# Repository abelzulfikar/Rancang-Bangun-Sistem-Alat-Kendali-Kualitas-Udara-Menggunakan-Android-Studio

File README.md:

# Rancang-Bangun-Sistem-Alat-Kendali-Kualitas-Udara-Menggunakan-Android-Studio
memantau dan mengatur kualitas udara dalam ruangan melalui aplikasi Android

Latar Belakang
Kualitas udara dalam ruangan memiliki dampak besar pada kesehatan dan kenyamanan manusia sehari-hari. Udara yang tercemar dapat menyebabkan gangguan pernapasan, alergi, dan dampak negatif lainnya. Karena banyaknya waktu yang dihabiskan di dalam ruangan, baik di tempat tinggal maupun tempat kerja, pengendalian kualitas udara menjadi penting. Diperlukan alat Sistem Kendali Kualitas Udara dengan sensor MQ 135 untuk mendeteksi udara tidak sehat, sensor GP2Y1010AU0F untuk sensitivitas debu, dan penambahan filter H13 atau HEPA untuk menyaring udara dari kotoran

Menghubungkan alat melalui socket AC ke sumber listrik.
1. Menghubungkan ESP 32 dengan jaringan Wi-Fi yang memiliki akses internet
2. Buka aplikasi "Freshism" yang sudah diinstal pada smartphone
3. Sensor akan membaca nilai udara dan debu dan hasilnya akan tampil di aplikasi
4. Tekan Tombol ON untuk mengaktifkan Kipas DC
5. Pilih Mode "Auto" pada tombol aplikasi "Freshism"
6. jika indikator kualitas udara tidak sehat, maka indikator led akan berwarna merah, tampilan aplikasi tidak sehat, dan kipas dc menyala

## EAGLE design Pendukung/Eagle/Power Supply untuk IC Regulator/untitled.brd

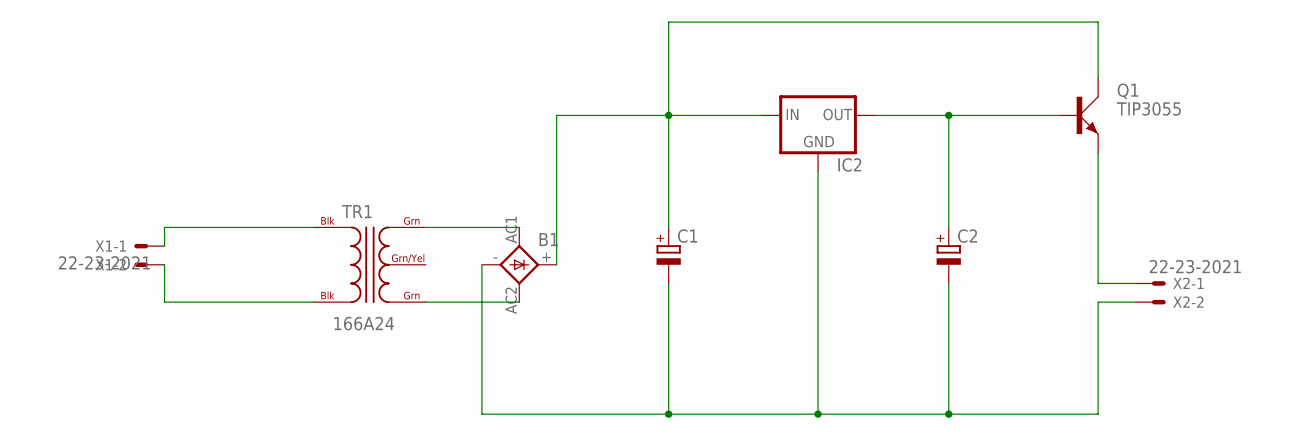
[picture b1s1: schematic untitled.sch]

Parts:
B1: FB32
C1: CPOL-EUE7.5-16; E7,5-16
C2: CPOL-EUE3.5-8; E3,5-8
IC2: 78XXL
Q1: TIP3055; TOP3AV
TR1: 166A24; C2H
X1, X2: 22-23-2021

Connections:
unnamed: TR1.BLK@1 (BLK), X1.1
unnamed: TR1.BLK@2 (BLK), X1.2
unnamed: B1.AC1, TR1.GRN@1 (GRN)
unnamed: B1.AC2, TR1.GRN@2 (GRN)
unnamed: B1.+, C1.+, IC2.IN, Q1.C
unnamed: B1.-, C1.-, C2.-, IC2.GND, X2.2
unnamed: Q1.E, X2.1
unnamed: C2.+, IC2.OUT, Q1.B

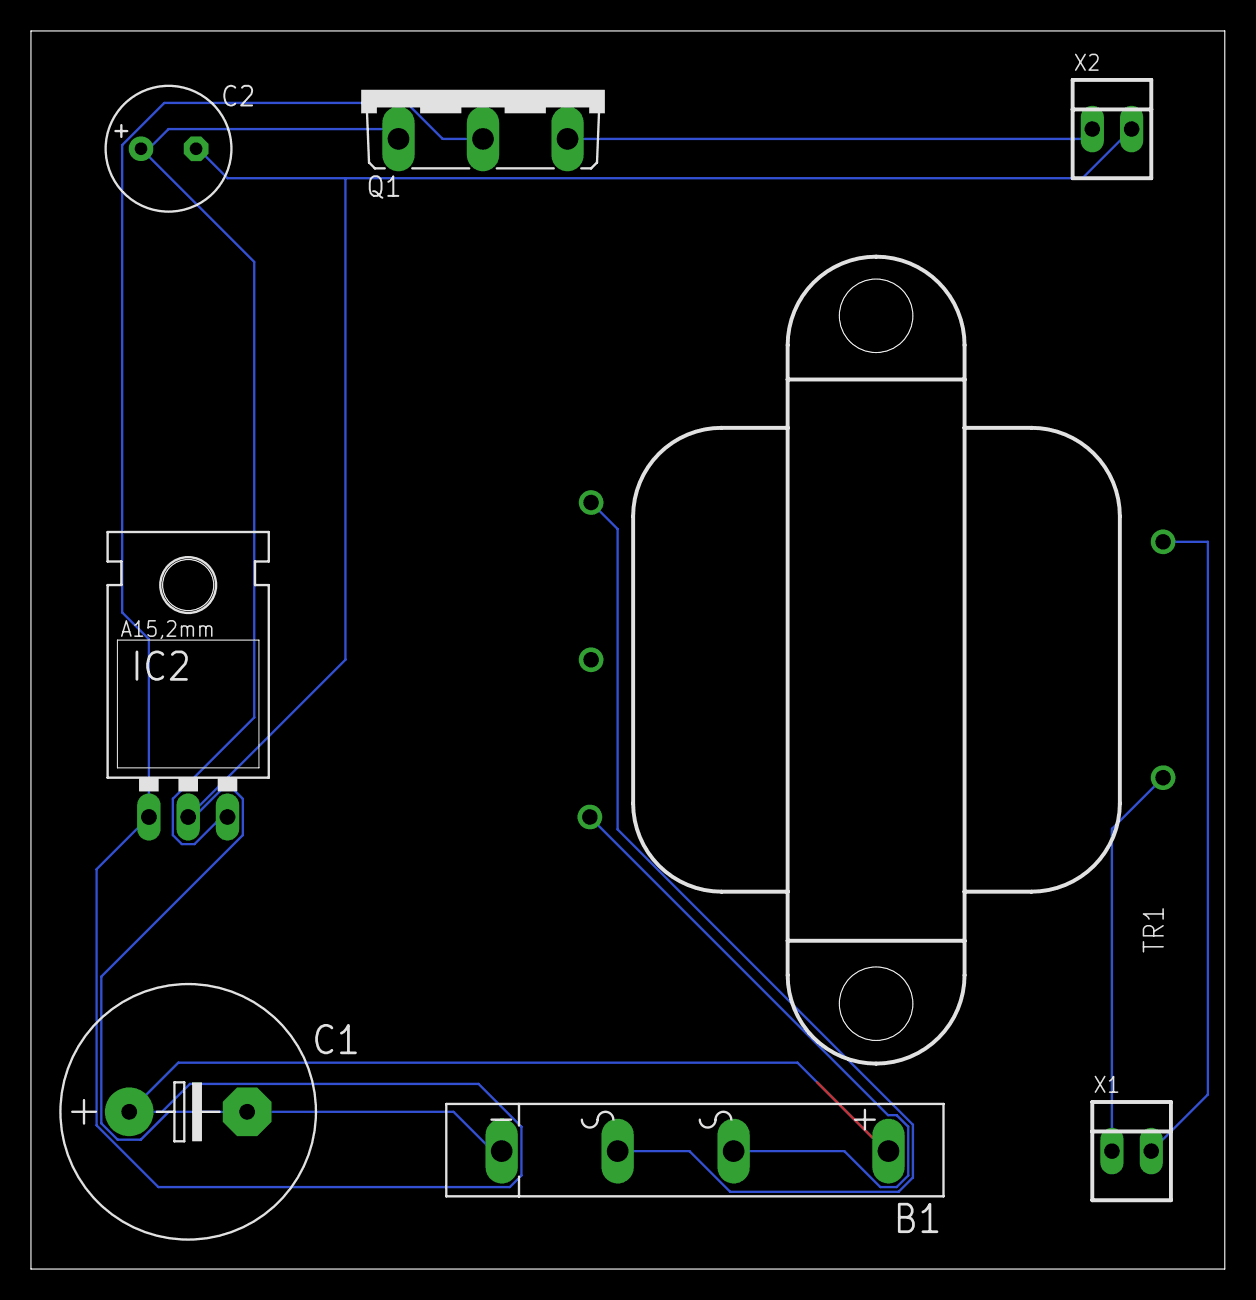
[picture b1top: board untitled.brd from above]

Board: 2 copper layers, 77.1 x 80.0 mm, 8 parts (0 on the bottom side), 8 nets.

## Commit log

2023-08-27 Rancang Bangun Sistem Alat Kendali Kualitas Udara
2023-08-27 Poster
2023-09-03 Rancang Bangun Sistem Alat Kendali Kualitas Udara Menggunakan Android
